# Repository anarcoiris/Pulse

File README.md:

# Pulse — PulseLab Forge

<div align="center">

</div>

```c
/**
 *    .,::::::   :::    .,::::::   .,-::::::::::::::::::::::::..       ...   :::.    :::.:::  .,-::::: .::::::. 
 *    ;;;;''''   ;;;    ;;;;'''' ,;;;'````';;;;;;;;'''';;;;``;;;;   .;;;;;;;.`;;;;,  `;;;;;;,;;;'````';;;`    ` 
 *     [[cccc    [[[     [[cccc  [[[            [[      [[[,/[[['  ,[[     \[[,[[[[[. '[[[[[[[[       '[==/[[[[,
 *     $$""""    $$'     $$""""  $$$            $$      $$$$$$c    $$$,     $$$$$$ "Y$c$$$$$$$$         '''    $
 *     888oo,__ o88oo,.__888oo,__`88bo,__,o,    88,     888b "88bo,"888,_ _,88P888    Y88888`88bo,__,o,88b    dP
 *     """"YUMMM""""YUMMM""""YUMMM "YUMMMMMP"   MMM     MMMM   "W"   "YMMMMMP" MMM     YMMMM  "YUMMMMMP""YMmMY" 
 *                      .,-::::: :::::::..    :::.    .-:::::'::::::::::::::                                    
 *                    ,;;;'````' ;;;;``;;;;   ;;`;;   ;;;'''' ;;;;;;;;'''','                                    
 *                    [[[         [[[,/[[['  ,[[ '[[, [[[,,==      [[                                           
 *                    $$$         $$$$$$c   c$$$cc$$$c`$$$"``      $$                                           
 *                    `88bo,__,o, 888b "88bo,888   888,888         88,                                          
 *                      "YUMMMMMP"MMMM   "W" YMM   ""` "MM,        MMM                                          
 */
```

**⚡ Unified Circuit Editor & MNA Simulator with Algorithmic PCB Layout & Autonomous MCP Hardware Synthesis**

---

> 🚧 **Active Development.** Architecture and generative pipelines evolve continuously — check [`docs/status/FORGE_STATUS.md`](docs/status/FORGE_STATUS.md) for live metrics and [`docs/status/CURRENT_SPRINT.md`](docs/status/CURRENT_SPRINT.md) for current active sprint tasks.

---

## 🎯 What is Pulse?

**PulseLab Forge** is a unified Modified Nodal Analysis (MNA) circuit editor, generative PCB synthesis engine, and hardware manufacturing pipeline. It bridges conceptual schematics to production-ready manufacturing deliverables (Gerbers, Drill files, CPL, BOM, and KiCad 8+/10 S-expressions) without leaving a single programmatic workflow.

Unlike standard CAD packages, Pulse incorporates:
1. **Procedural PCB Layout Engine**: Force-directed attraction/repulsion, thermal via matrix generator, ground plane manager with inter-layer via stitching, and Specctra DSN/FreeRouting auto-routing bridge.
2. **Multi-Provider Supply Chain Engine**: Live component fetching from **JLCPCB (LCSC)** and **PCBWay** catalogs with local 24h disk caching and interactive component candidate decision matching.
3. **Local FastMCP Server (36 Tools)**: Exposes structural circuit design, schematic cross-checks, DRC verification, thermal calculation, and CAM exports directly to LLM agents (Claude Desktop, Ollama, etc.).

---

## 🛠️ Main Features & Modules

| Module | Location | Description |
|---|---|---|
| 🖥️ **MNA Simulator & UI** | `pulse_lab.py` | PyGame visual editor with anti-aliased rendering, real-time MNA solver, live oscilloscope, and interactive passive/active components. |
| 🌐 **FastAPI Web Backend** | `app/` | REST API gateway, WebSocket streaming, LLM session manager, and FastMCP bridge. |
| 🎨 **Web EDA Studio** | `webapp/` | Modern React/Vite/Three.js web canvas with 2D/3D PCB viewer, AI chat assistant, and BOM tables. |
| 📐 **Algorithmic PCB Builder** | `bridge/pcb_builder.py` | Generates KiCad 8+/10 S-expressions, coordinates auto-placement heuristics, thermal pads, and DRC gates. |
| 📍 **2D Auto-Placement Engine** | `core/auto_placement.py` | Physics-based placement relaxation using Hooke attraction, Coulomb pin repulsion, and domain orientation rules. |
| ⚡ **Thermal Management Engine** | `core/thermal_engine.py` | Automated $3 \times 3$ thermal via grids under high-power pads (e.g. ESP32 EPAD 41, AMS1117 tab) with solid zone connections. |
| 🛡️ **Ground Zone & Via Stitching** | `core/copper_zone_manager.py` | Automated double-sided `PWR_GND` ground pours, $0.50\,\text{mm}$ thermal peninsulas, and matrix inter-layer ground via stitching. |
| 📦 **Multi-Provider Fetcher Engine** | `core/providers/` | Live side-by-side component search across **JLCPCB (LCSC)** and **PCBWay** with Basic/Extended library detection and local caching. |
| 🎨 **Graphics & Stencil Engine** | `bridge/graphics_engine.py` | Converts DXF/SVG vector artwork into silk/copper KiCad polygon primitives (`gr_poly`). |
| 🛣️ **FreeRouting Auto-Router Bridge** | `bridge/freerouting_bridge.py` | DSN export (`kicad-cli pcb export dsn`), headless FreeRouting CLI runner, and SES back-annotation import. |
| 📑 **100% SCH $\leftrightarrow$ PCB Parity** | `core/sch_pcb_crosscheck.py` | Automatic net and symbol cross-check gate embedded into DRC validation. |
| 🧠 **MCP Server (36 Tools)** | `mcp_server/` | FastMCP service exposing complete hardware synthesis capabilities to external LLM client apps. |

---

## 🚀 Quick Start

### Prerequisites

- **Python 3.10+**
- **KiCad 8+ or KiCad 10+** (in `PATH` for Gerber/Drill generation and SVG export via `kicad-cli`)
- *(Optional)* **Node.js 18+** for running the Web Studio locally.
- *(Optional)* **Ollama** running locally on `:11434` or `:11431` for Forge Studio LLM agent features.

### Installation

```bash
git clone https://github.com/anarcoiris/Pulse.git
cd Pulse
pip install -r requirements.txt
```

### Launch the Visual Circuit Editor & Simulator (PyGame Desktop)

```bash
python pulse_lab.py
```

### Launch the Full Web Studio (FastAPI + Vite React Canvas)

```powershell
./scripts/launch-pulselab.ps1
```

### Run Full Test Suite (198 Unit Tests)

```bash
python -m pytest tests/
```

---

## 📁 Repository Structure

```
Pulse/
├── app/                  ← FastAPI backend gateway, synthesis orchestrator & WebSockets
├── bridge/               ← KiCad compilation, S-expressions, graphics & auto-routing
├── core/                 ← Physics simulation, placement algorithms, supply chain & audit gates
├── docs/                 ← Project documentation, architectural blueprints & how-to guides
├── examples/             ← Python runnable examples and demonstration circuits
├── knowledge/            ← RAG knowledge base, prompt templates & agent engines
├── mcp_server/           ← Local FastMCP server (36 exposed tools)
├── presets/              ← Circuit templates (ESP32 DevKit, EMP PFN, MCU UART)
├── scripts/              ← Automation scripts, pipeline validation & stack launchers
├── skills/               ← Hardware synthesis agent skills and KiCad adapters
├── studio/               ← Forge Studio headless LLM REPL (`python -m studio`)
├── tests/                ← Pytest regression suite (198 tests, 100% passing)
├── ui/                   ← PyGame desktop simulator GUI & oscilloscope
├── webapp/               ← Modern React / Vite / Three.js Web Studio frontend
├── .github/              ← GitHub Actions CI & Docker image release pipelines
├── Caddyfile / Dockerfile / docker-compose.pulselab.yml
├── pulse_lab.py          ← Desktop circuit simulator entrypoint
└── Pulse_cfg.json        ← Unified platform configuration (SSOT)
```

---

## 🎬 Modos de Uso / Execution Modes

### 1. Main PyGame UI Simulator

```bash
python pulse_lab.py
```

### 2. Forge Studio (Headless LLM Debug REPL)

```powershell
python -m studio
```

Session log transcripts are stored under `knowledge/data/llm_sessions/sessions/{session_id}/`.

### 3. MCP Server (Claude Desktop / Agent Integration)

```bash
python -m mcp_server.server
```

---

## 📚 Documentation Map

| Document | Purpose |
|---|---|
| [`docs/README.md`](docs/README.md) | Complete documentation index and doc roles |
| [`docs/status/CURRENT_SPRINT.md`](docs/status/CURRENT_SPRINT.md) | Active sprint execution order & next actions |
| [`docs/status/FORGE_STATUS.md`](docs/status/FORGE_STATUS.md) | Verified system metrics (tests, RAG, MCP tools) |
| [`docs/roadmap.md`](docs/roadmap.md) | Product phases & feature roadmap |
| [`docs/architecture/APP_ARCHITECTURE.md`](docs/architecture/APP_ARCHITECTURE.md) | System architecture & layer isolation rules |

---

## 📄 License

Distributed under the **Apache License 2.0**. See [`LICENSE`](LICENSE) for details.

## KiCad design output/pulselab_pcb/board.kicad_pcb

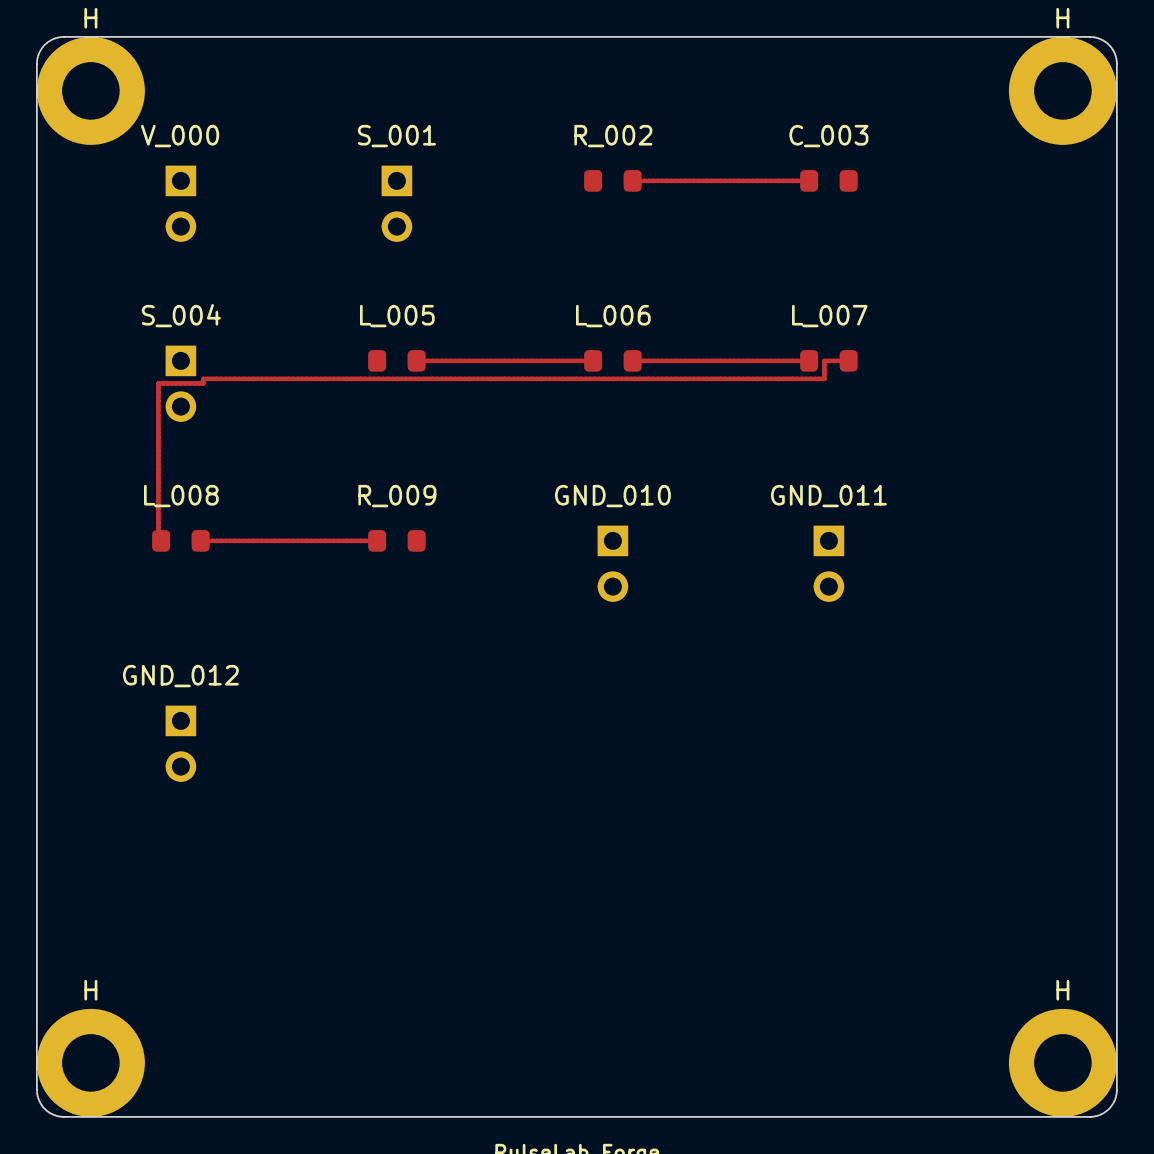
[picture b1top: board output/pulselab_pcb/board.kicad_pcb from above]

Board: 2 copper layers, 60.0 x 60.0 mm, 17 parts (0 on the bottom side), 6 nets.

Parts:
C_003: 6e-07; C_0805_2012Metric
GND_010, GND_011, GND_012: GND; PinHeader_1x02_P2.54mm_Vertical
H: MountingHole_3.2mm_M3
H#2, H#3, H#4: MountingHole_3.2mm_M3
L_005, L_006, L_007, L_008: 2.5e-07; L_0805_2012Metric
R_002: 10000; R_0805_2012Metric
R_009: 50; R_0805_2012Metric
S_001, S_004: S; PinHeader_1x02_P2.54mm_Vertical
V_000: 5000V; PinHeader_1x02_P2.54mm_Vertical

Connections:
ANT_IN: L_008.2, R_009.1
BANCO: C_003.1, R_002.2
GND: C_003.2, R_009.2
PFN1: L_005.2, L_006.1
PFN2: L_006.2, L_007.1
PFN3: L_007.2, L_008.1

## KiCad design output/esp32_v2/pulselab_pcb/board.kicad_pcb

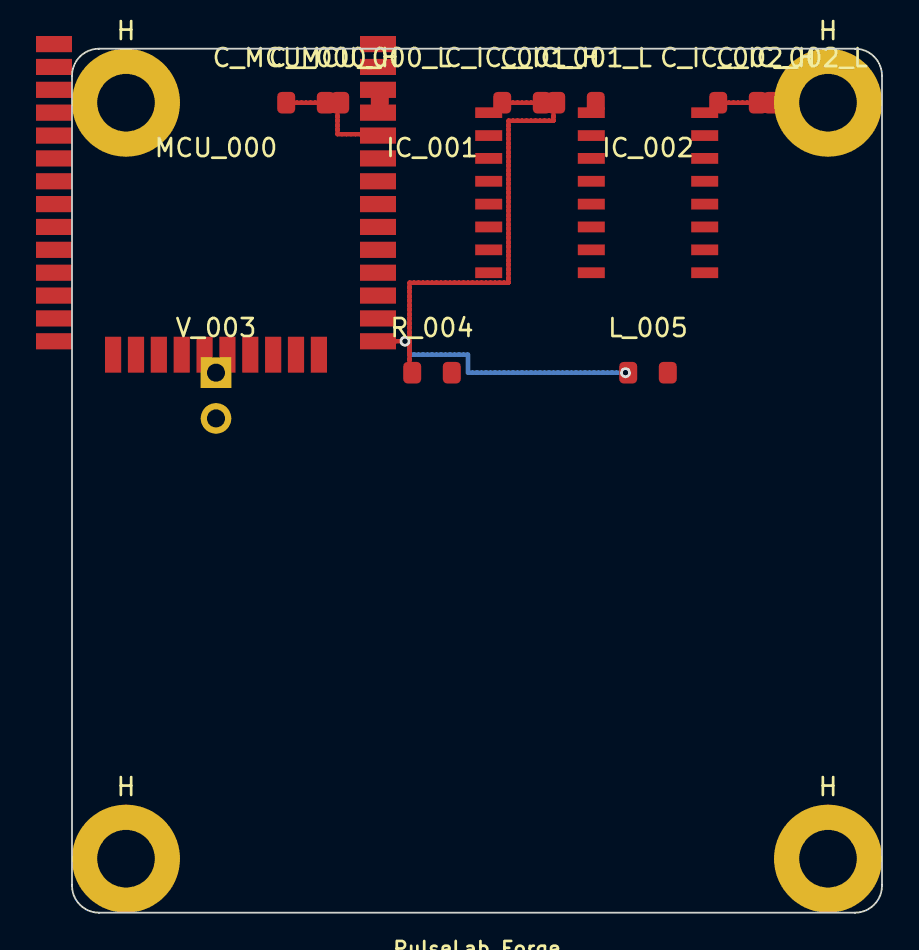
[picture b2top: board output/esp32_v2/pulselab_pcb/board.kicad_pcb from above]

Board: 2 copper layers, 45.0 x 48.0 mm, 16 parts (0 on the bottom side), 7 nets.

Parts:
C_IC_001_H, C_IC_002_H: 10uF; C_0805_2012Metric
C_IC_001_L, C_IC_002_L: 100nF; C_0805_2012Metric
C_MCU_000_H: 10uF; C_0805_2012Metric
C_MCU_000_L: 100nF; C_0805_2012Metric
H: MountingHole_3.2mm_M3
H#2, H#3, H#4: MountingHole_3.2mm_M3
IC_001: 3.3; SOIC-16_3.9x9.9mm_P1.27mm
IC_002: 5; SOIC-16_3.9x9.9mm_P1.27mm
L_005: 0.02; L_0805_2012Metric
MCU_000: RF_Module:ESP32-WROOM-32; ESP32
R_004: 10000; R_0805_2012Metric
V_003: 5V; PinHeader_1x02_P2.54mm_Vertical

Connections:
3V3: C_IC_001_H.1, C_IC_001_L.1, C_MCU_000_H.1, C_MCU_000_L.1, IC_001.2, MCU_000.2, R_004.1
EN: MCU_000.3, R_004.2
GND: C_IC_001_H.2, C_IC_001_L.2, C_IC_002_H.2, C_IC_002_L.2, C_MCU_000_H.2, C_MCU_000_L.2, IC_001.1, IC_002.1, L_005.2, MCU_000.1, MCU_000.38
IO2: L_005.1, MCU_000.25
RXD0: IC_002.3, MCU_000.31
TXD0: IC_002.2, MCU_000.30
VBUS: C_IC_002_H.1, C_IC_002_L.1, IC_001.3, IC_002.16

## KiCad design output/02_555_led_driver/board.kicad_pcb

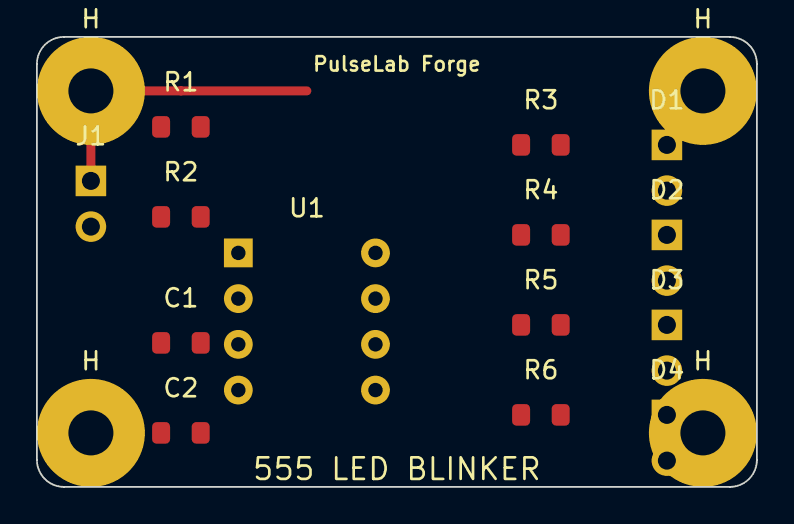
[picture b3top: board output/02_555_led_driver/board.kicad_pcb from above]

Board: 2 copper layers, 40.0 x 25.0 mm, 18 parts (0 on the bottom side), 5 nets.

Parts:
C1: 10uF; C_0805_2012Metric
C2: 100nF; C_0805_2012Metric
D1, D2, D3, D4: LED; PinHeader_1x02_P2.54mm_Vertical
H: MountingHole_2.5mm_M3
H#2, H#3, H#4: MountingHole_2.5mm_M3
J1: VCC/GND; PinHeader_1x02_P2.54mm_Vertical
R1: 10k; R_0805_2012Metric
R2: 47k; R_0805_2012Metric
R3, R4, R5, R6: 330; R_0805_2012Metric
U1: NE555; DIP-8_W7.62mm

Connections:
DIS: R1.2, R2.1
GND: C1.2, C2.2
OUT: R3.1, R4.1, R5.1, R6.1
THR: C1.1, R2.2
VCC: C2.1, R1.1

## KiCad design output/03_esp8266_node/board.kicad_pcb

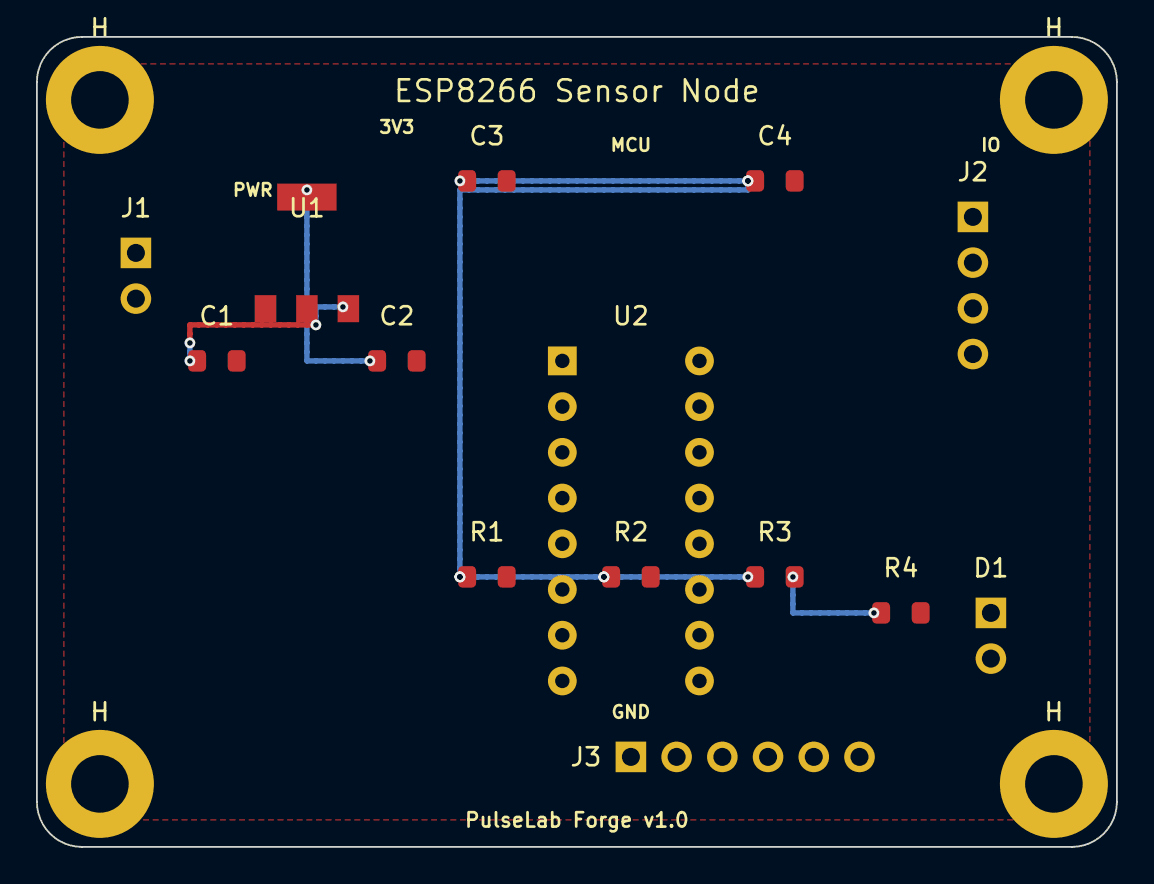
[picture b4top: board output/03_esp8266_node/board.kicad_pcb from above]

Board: 2 copper layers, 60.0 x 45.0 mm, 18 parts (0 on the bottom side), 4 nets.

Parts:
C1, C2: 10uF; C_0805_2012Metric
C3, C4: 100nF; C_0805_2012Metric
D1: LED; PinHeader_1x02_P2.54mm_Vertical
H: MountingHole_3.2mm_M3
H#2, H#3, H#4: MountingHole_3.2mm_M3
J1: 5V IN; PinHeader_1x02_P2.54mm_Vertical
J2: I2C Sensor; PinHeader_1x04_P2.54mm_Vertical
J3: UART PROG; PinHeader_1x06_P2.54mm_Vertical
R1, R2, R3: 10k; R_0805_2012Metric
R4: 330; R_0805_2012Metric
U1: AMS1117-3.3; SOT-223-3_TabPin2
U2: ESP-12F; DIP-16_W7.62mm

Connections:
3V3: C2.1, C3.1, C4.1, R1.1, R2.1, R3.1, U1.2
5V: C1.1, U1.3
GND: C1.2, C2.2, C3.2, C4.2, U1.1
GPIO2: R3.2, R4.1

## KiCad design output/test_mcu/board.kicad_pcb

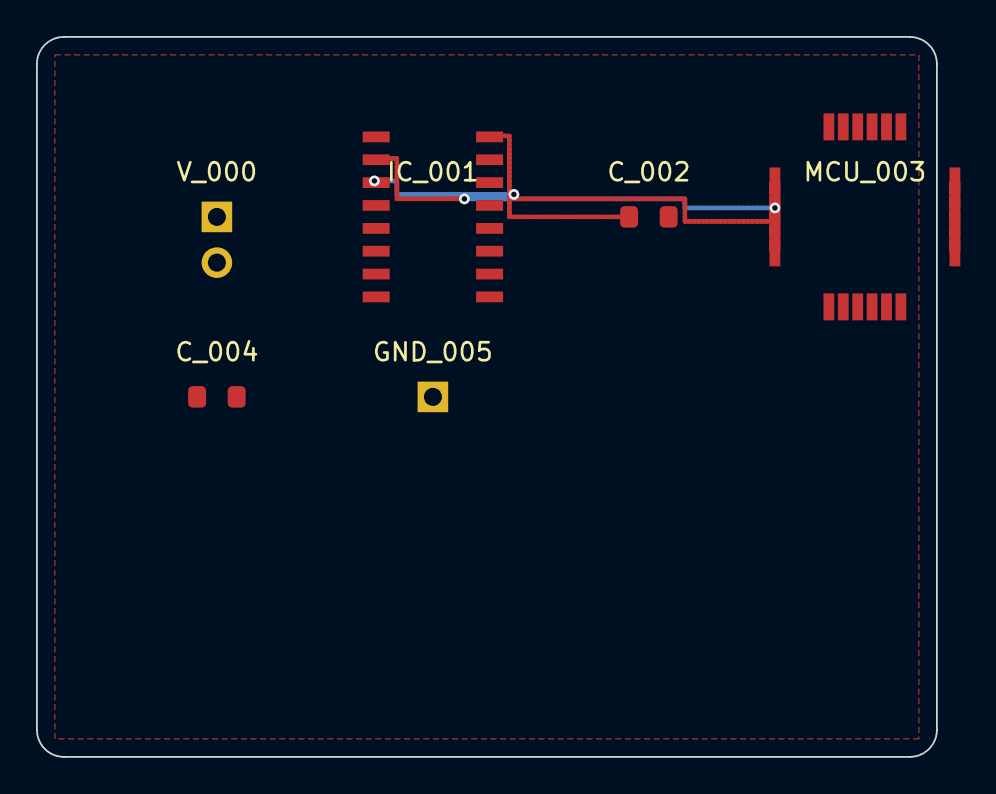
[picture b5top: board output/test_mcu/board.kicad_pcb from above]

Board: 2 copper layers, 50.0 x 40.0 mm, 6 parts (0 on the bottom side), 5 nets.

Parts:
C_002: 1e-07; C_0805_2012Metric
C_004: 1e-05; C_0805_2012Metric
GND_005: GND; PinHeader_1x01_P2.54mm_Vertical
IC_001: CH340C; SOIC-16_3.9x9.9mm_P1.27mm
MCU_003: ESP8266_Node; TQFP-24_7x7mm_P0.80mm
V_000: V; PinHeader_1x02_P2.54mm_Vertical

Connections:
GND: C_002.2, C_004.2, IC_001.1, MCU_003.15
MCU_RX: IC_001.2, MCU_003.21
MCU_TX: IC_001.3, MCU_003.22
VCC33: C_004.1, IC_001.4, MCU_003.8
VUSB: C_002.1, IC_001.16

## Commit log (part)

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2026-04-18 wdss
2026-04-20 chore: update dependencies and project artifacts
2026-04-21 feat: implement PCB editor with component placement, multi-selection, and wire routing capabilities
2026-04-21 chore: refresh git cache and synchronize repository based on new .gitignore
2026-04-25 feat: implement PCB synthesis engine, LLM circuit parser, and automated KiCad fabrication workflow integration
2026-04-27 feat: integrate GNN layout modeling and reorganize core circuit engine into project structure
2026-05-03 feat: add KiCad schematic source files and corresponding training datasets to the knowledge base
2026-05-03 feat: implement hardware pinout dictionary and complex circuit validation suite
2026-05-03 data: ingest raw kicad files and training samples
2026-05-03 feat: initialize knowledge training pipeline with KiCad dataset and supporting utility scripts

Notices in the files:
README.md:
License: Apache 2.0
